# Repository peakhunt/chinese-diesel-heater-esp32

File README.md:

# Hello World Example

Dangerous! No safety functions implemented on purpose of  
full manual control!

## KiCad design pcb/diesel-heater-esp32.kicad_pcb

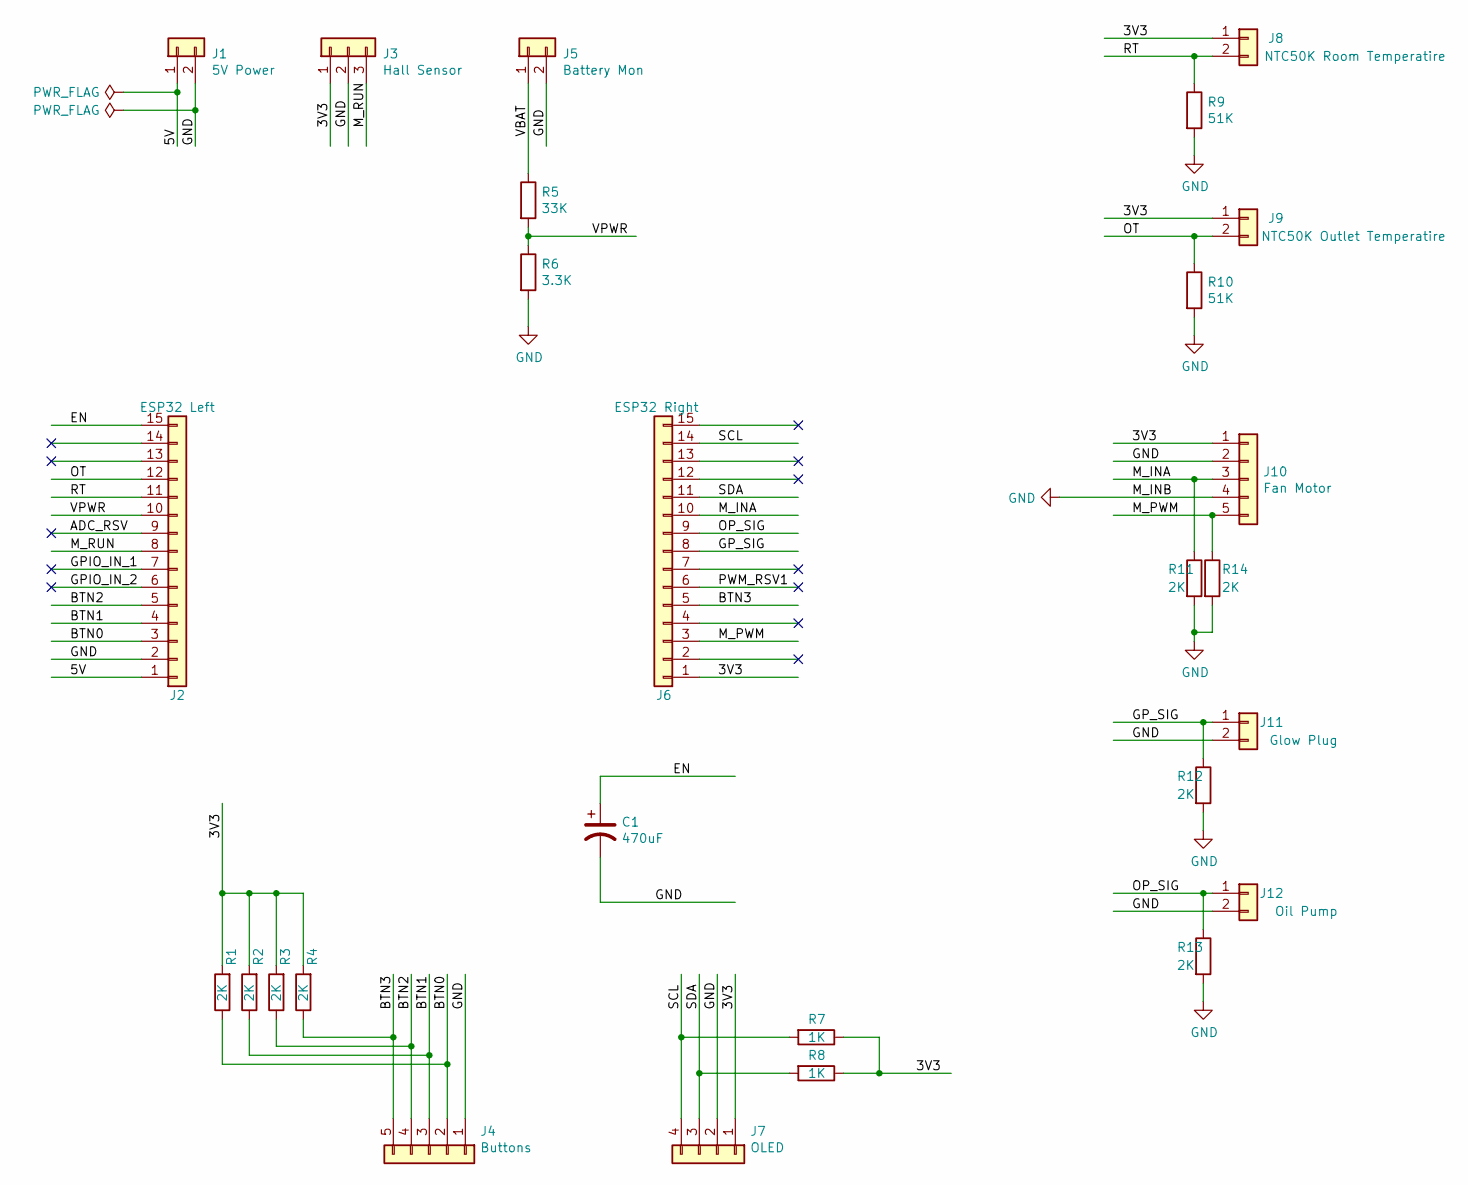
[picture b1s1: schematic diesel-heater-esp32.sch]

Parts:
C1: 470uF; CP_Radial_D6.3mm_P2.50mm
J1: 5V Power; JST_EH_B2B-EH-A_1x02_P2.50mm_Vertical
J2: ESP32 Left; PinSocket_1x15_P2.54mm_Vertical
J3: Hall Sensor; JST_EH_B3B-EH-A_1x03_P2.50mm_Vertical
J4: Buttons; JST_EH_B5B-EH-A_1x05_P2.50mm_Vertical
J5: Battery Mon; JST_EH_B2B-EH-A_1x02_P2.50mm_Vertical
J6: ESP32 Right; PinSocket_1x15_P2.54mm_Vertical
J7: OLED; JST_EH_B4B-EH-A_1x04_P2.50mm_Vertical
J8: NTC50K Room Temperatire; JST_EH_B2B-EH-A_1x02_P2.50mm_Vertical
J9: NTC50K Outlet Temperatire; JST_EH_B2B-EH-A_1x02_P2.50mm_Vertical
J10: Fan Motor; JST_EH_B5B-EH-A_1x05_P2.50mm_Vertical
J11: Glow Plug; JST_EH_B2B-EH-A_1x02_P2.50mm_Vertical
J12: Oil Pump; JST_EH_B2B-EH-A_1x02_P2.50mm_Vertical
R1, R2, R3, R4, R11, R12, R13, R14: 2K; R_0603_1608Metric_Pad0.98x0.95mm_HandSolder
R5: 33K; R_0603_1608Metric_Pad0.98x0.95mm_HandSolder
R6: 3.3K; R_0603_1608Metric_Pad0.98x0.95mm_HandSolder
R7, R8: 1K; R_0603_1608Metric_Pad0.98x0.95mm_HandSolder
R9, R10: 51K; R_0603_1608Metric_Pad0.98x0.95mm_HandSolder

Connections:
/3V3: J3.1, J6.1, J7.1, J8.1, J9.1, J10.1, R1.2, R2.2, R3.2, R4.2, R7.1, R8.1
/5V: J1.1, J2.1
/ADC_RSV: J2.9
/BTN0: J2.3, J4.2, R1.1
/BTN1: J2.4, J4.3, R2.1
/BTN2: J2.5, J4.4, R3.1
/BTN3: J4.5, J6.5, R4.1
/EN: C1.1, J2.15
/GPIO_IN_1: J2.7
/GPIO_IN_2: J2.6
/GP_SIG: J6.8, J11.1, R12.1
/M_INA: J6.10, J10.3, R11.1
/M_PWM: J6.3, J10.5, R14.1
/M_RUN: J2.8, J3.3
/OP_SIG: J6.9, J12.1, R13.1
/OT: J2.12, J9.2, R10.1
/PWM_RSV1: J6.6
/RT: J2.11, J8.2, R9.1
/SCL: J6.14, J7.4, R7.2
/SDA: J6.11, J7.3, R8.2
/VBAT: J5.1, R5.1
/VPWR: J2.10, R5.2, R6.1
GND: C1.2, J1.2, J2.2, J3.2, J4.1, J5.2, J7.2, J10.2, J10.4, J11.2, J12.2, R6.2, R9.2, R10.2, R11.2, R12.2, R13.2, R14.2

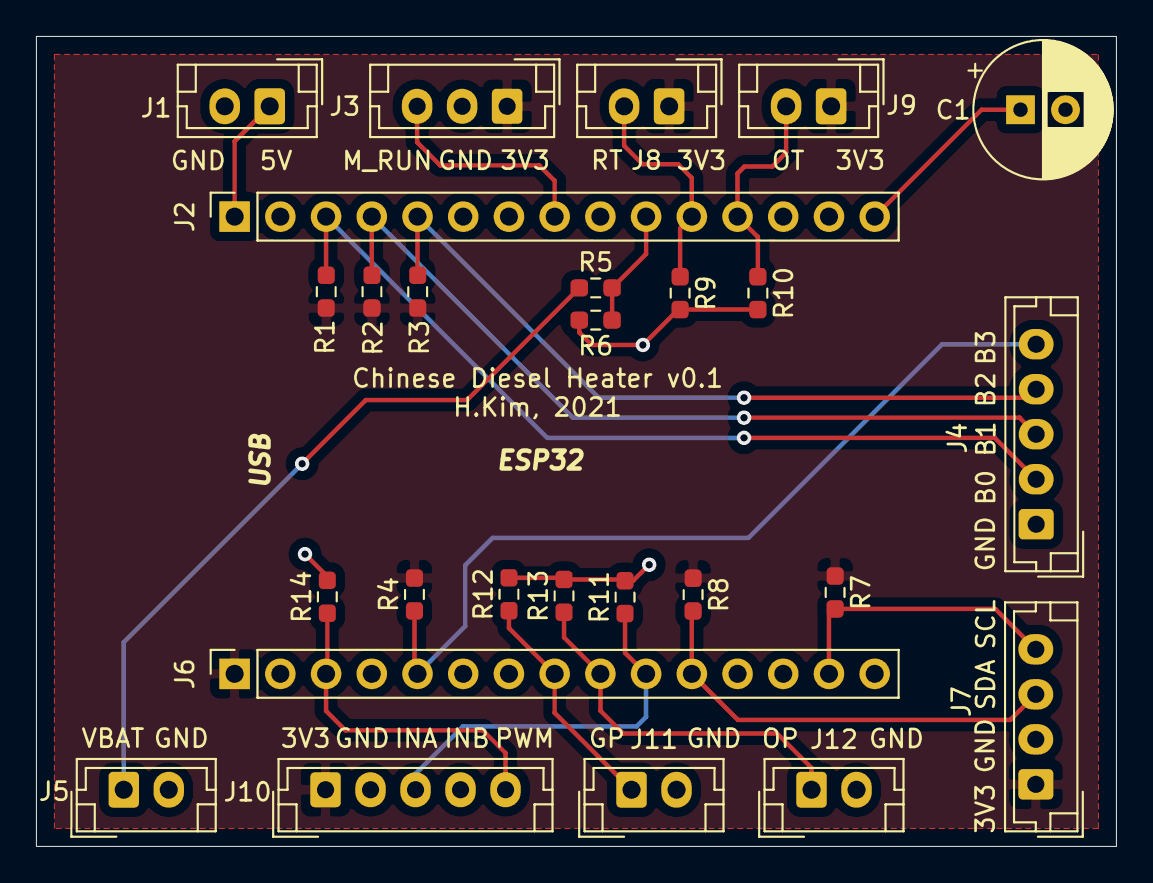
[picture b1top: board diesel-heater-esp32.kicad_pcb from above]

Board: 2 copper layers, 60.0 x 45.0 mm, 27 parts (0 on the bottom side), 19 nets.

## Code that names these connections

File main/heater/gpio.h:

#ifndef __GPIO_DEF_H__
#define __GPIO_DEF_H__

#include <stdbool.h>

typedef enum
{
  gpio_out_pin_5,
  gpio_out_pin_18,
  gpio_out_pin_19,
} gpio_out_pin_t;
#define GPIO_MAX_OUTPUT   (gpio_out_pin_19 + 1)

typedef enum
{
  gpio_in_pin_25,
  gpio_in_pin_26,
  gpio_in_pin_27,

  gpio_in_pin_13,   // BTN0
  gpio_in_pin_12,   // BTN1
  gpio_in_pin_14,   // BTN2
  gpio_in_pin_4,    // BTN3

} gpio_in_pin_t;
#define GPIO_MAX_INPUT    (gpio_in_pin_4 + 1)

typedef enum
{
  gpio_input_state_low,
  gpio_input_state_low_to_high,
  gpio_input_state_high,
  gpio_input_state_high_to_low,
} gpio_input_state_t;

typedef void (*gpio_listener)(gpio_in_pin_t pin, gpio_input_state_t state, void* arg);

extern void gpio_init(void);
extern void gpio_set(gpio_out_pin_t pin, bool v);
extern bool gpio_get(gpio_in_pin_t pin);
extern void gpio_set_debounce(gpio_in_pin_t pin, bool debounce);
extern void gpio_listen(gpio_in_pin_t pin, gpio_listener listener, void* arg);
extern gpio_input_state_t gpio_get_state(gpio_in_pin_t pin);

#endif /* !__GPIO_DEF_H__ */

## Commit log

2020-12-14 first commit.
2020-12-17 finishing up esp32 version of heater controller
2020-12-18 adding web server
2021-01-18 finishing wifi
2021-01-18 working on web front
2021-01-19 working on svg icons
2021-01-20 working web front end
2021-01-25 working on rest api
2021-01-26 fixed unstable connection issue
2021-01-26 minor layout change
2021-01-26 Create LICENSE
2021-01-26 readme update
2021-01-26 working on temperature trand
2021-01-26 added support for temperature unit
2021-01-28 bug fixed for range check
2021-01-28 to prevent float point nan case
2021-01-28 worked on settings dialog
2021-01-28 changed esp32 settings for maximum performance
2021-01-28 added gziped content support
2021-01-28 added compressed html content
2021-01-29 changed for v-dialog components to use v-model
2021-02-01 close button bug fix
2021-02-01 moved axios call to store for max portability
2021-02-02 adding ifdef-loader for electron/serial based controller interface
2021-02-02 ifdef-loader config
2021-02-02 package.json cleanup
2021-02-02 add serialport and electron-rebuild
2021-02-02 added missing background.js
2021-02-02 added electron builder plugin option
2021-02-02 working on serialport
2021-02-02 changed to use action to start polling
2021-02-02 removed unused property
2021-02-05 a huge commit before working on serial cli based electron app
2021-02-05 a simple bug fix while migrating
2021-02-05 cli interface bug fix
2021-02-05 a bunch of cli apis
2021-02-05 added to start polling upon comm port open
2021-02-05 disabled gzip build for electron
2021-02-05 added electron rebuild command for serialport rebuild
2021-02-05 changed prompt to Heater>
2021-02-06 serialport module malfunctioning upon build
2021-02-08 more flexible command prompt detection
2021-02-08 working on settings cli interface
2021-02-08 added settings related cli api
2021-02-09 added dynamic layout
2021-02-13 added motor enable/disable pin for 3.3V to 5V inconvenience
2021-02-13 Revert "added motor enable/disable pin for 3.3V to 5V inconvenience"
    This reverts commit 5b280b5aa6429c6a0d15fb01282438d11590f488.
    this is a complete nonsense. we need a level shift ◙ircuit for enable pin as well.
    reverting commit and will look for a better level shifter IC.
2021-02-15 added cli save command after modifying settings
2021-02-15 fixed wrong comment
2021-02-15 in honor of chinese diesel heater that kept me warm in this winter
2021-02-20 added room temperature on electorn build. added dummy roomTemp on REST api
2021-02-23 bug fix in adc channel map for ntc50k. added room temperature
2021-02-23 added room temperature signal
2021-02-24 added more adc channels
2021-02-24 added M_INA pin
2021-02-24 preparing works for OLED with buttons
2021-02-24 working on OLED display
2021-02-25 code improvement. working on OLED display and buttons
2021-02-25 fixed pin conflict for OLED button3
2021-02-25 changed sys tick rate to 1KHz. changed heater task priority to max. set affinity of lwip task to cpu0
2021-02-25 a simple dirty hack for display which nobody cares
2021-02-25 adding pcb
2021-02-25 pcb text alignment
2021-02-25 capacitor value fixed. capacitor sized set to 6.3mm
2021-02-25 fixed bug in en bug workaround circult. capacitor should be connected to EN and grounded
2021-02-26 changed pcb layout to fit esp32 dimension
2021-02-26 releasing pcb 0.1
2022-06-09 adding how to build just to remember
